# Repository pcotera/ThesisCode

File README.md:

Hi there!

Here you can find all the code and data from the experiments and the graphs used in my PhD thesis. 

The folders are arranged by the chapters in the thesis where the code is used. 

If you have any questions please send me an email at pablo.cotera@mail.utoronto.ca or visit www.pcotera.com

Hope this helps!

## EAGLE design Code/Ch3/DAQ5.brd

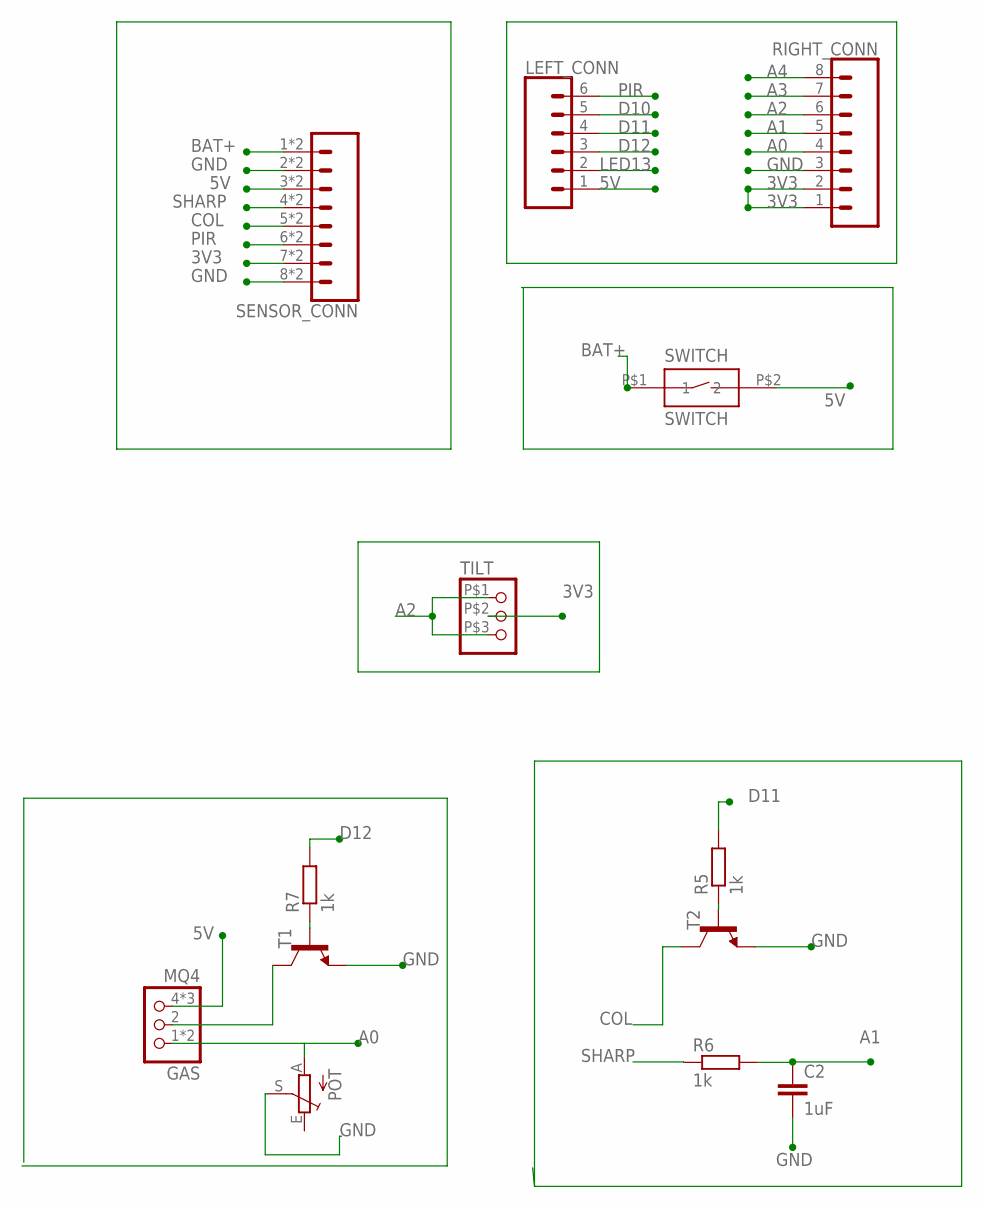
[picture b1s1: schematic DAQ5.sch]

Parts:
C2: 1uF; C5B2.5
GAS: MQ4; 6PIN_MQ
LEFT_CONN: CONN_06NO_SILK_FEMALE_PTH; 1X06_NO_SILK
POT: TRIM_EU-B25P; B25P
R5, R6, R7: 1k; R1206
RIGHT_CONN: CONN_08NO_SILK_FEMALE_PTH; 1X08_NO_SILK
SENSOR_CONN: CONN_08; PHOENIX08
SWITCH: SWITCH
T1, T2: -NPN-TO92-EBC; TO92-EBC
TILT: TILT

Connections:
3V3: RIGHT_CONN.1, RIGHT_CONN.2, SENSOR_CONN.7, SENSOR_CONN.P$7 (7), TILT.P$2 (2)
5V: GAS.4 (3), GAS.5 (3), GAS.6 (3), LEFT_CONN.1, SENSOR_CONN.3, SENSOR_CONN.P$3 (3), SWITCH.P$2 (2)
A0: GAS.1, GAS.3 (1), POT.A, RIGHT_CONN.4
A1: C2.1, R6.2, RIGHT_CONN.5
A2: RIGHT_CONN.6, TILT.P$1 (1), TILT.P$3 (3)
A3: RIGHT_CONN.7
A4: RIGHT_CONN.8
BAT+: SENSOR_CONN.1, SENSOR_CONN.P$1 (1), SWITCH.P$1 (1)
COL: SENSOR_CONN.5, SENSOR_CONN.P$5 (5), T2.C
D10: LEFT_CONN.5
D11: LEFT_CONN.4, R5.2
D12: LEFT_CONN.3, R7.2
GND: C2.2, POT.S, RIGHT_CONN.3, SENSOR_CONN.2, SENSOR_CONN.8, SENSOR_CONN.P$2 (2), SENSOR_CONN.P$8 (8), T1.E, T2.E
LED13: LEFT_CONN.2
unnamed: R5.1, T2.B
unnamed: GAS.2, T1.C
unnamed: R7.1, T1.B
PIR: LEFT_CONN.6, SENSOR_CONN.6, SENSOR_CONN.P$6 (6)
SHARP: R6.1, SENSOR_CONN.4, SENSOR_CONN.P$4 (4)

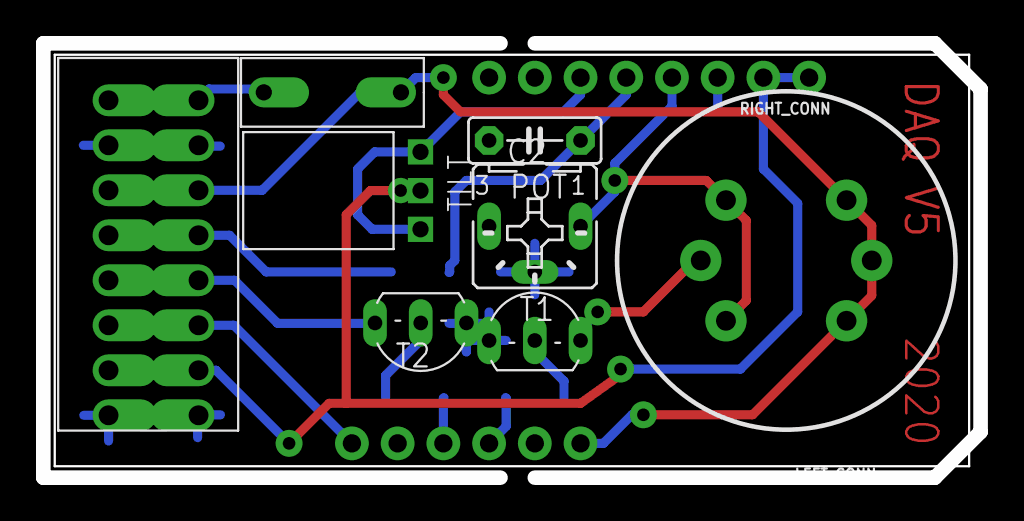
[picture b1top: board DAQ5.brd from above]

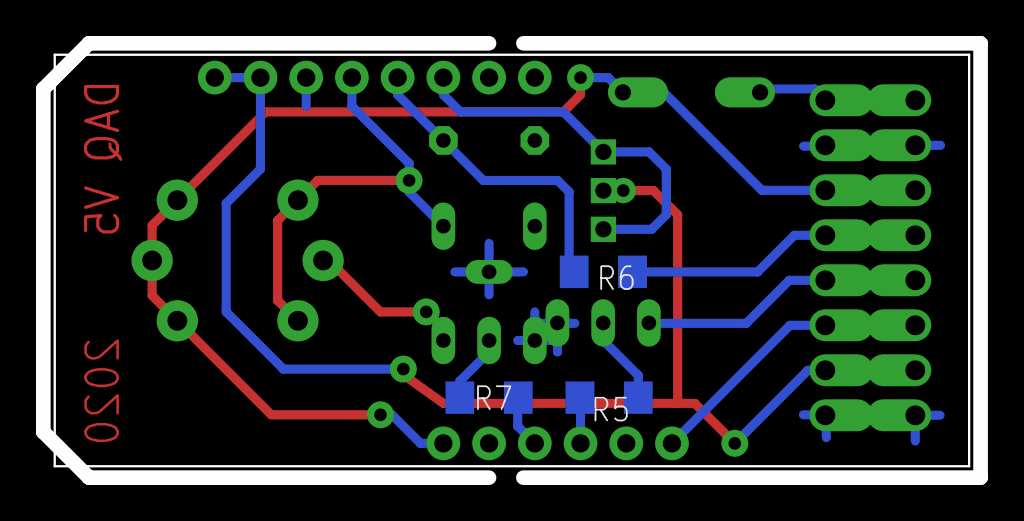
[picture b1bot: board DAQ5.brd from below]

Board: 2 copper layers, 52.1 x 24.1 mm, 13 parts (3 on the bottom side), 15 nets.

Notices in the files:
parts and their libraries:
SparkFun-Connectors: Licensing: Creative Commons ShareAlike 4.0 International - https://creativecommons.org/licenses/by-sa/4.0
